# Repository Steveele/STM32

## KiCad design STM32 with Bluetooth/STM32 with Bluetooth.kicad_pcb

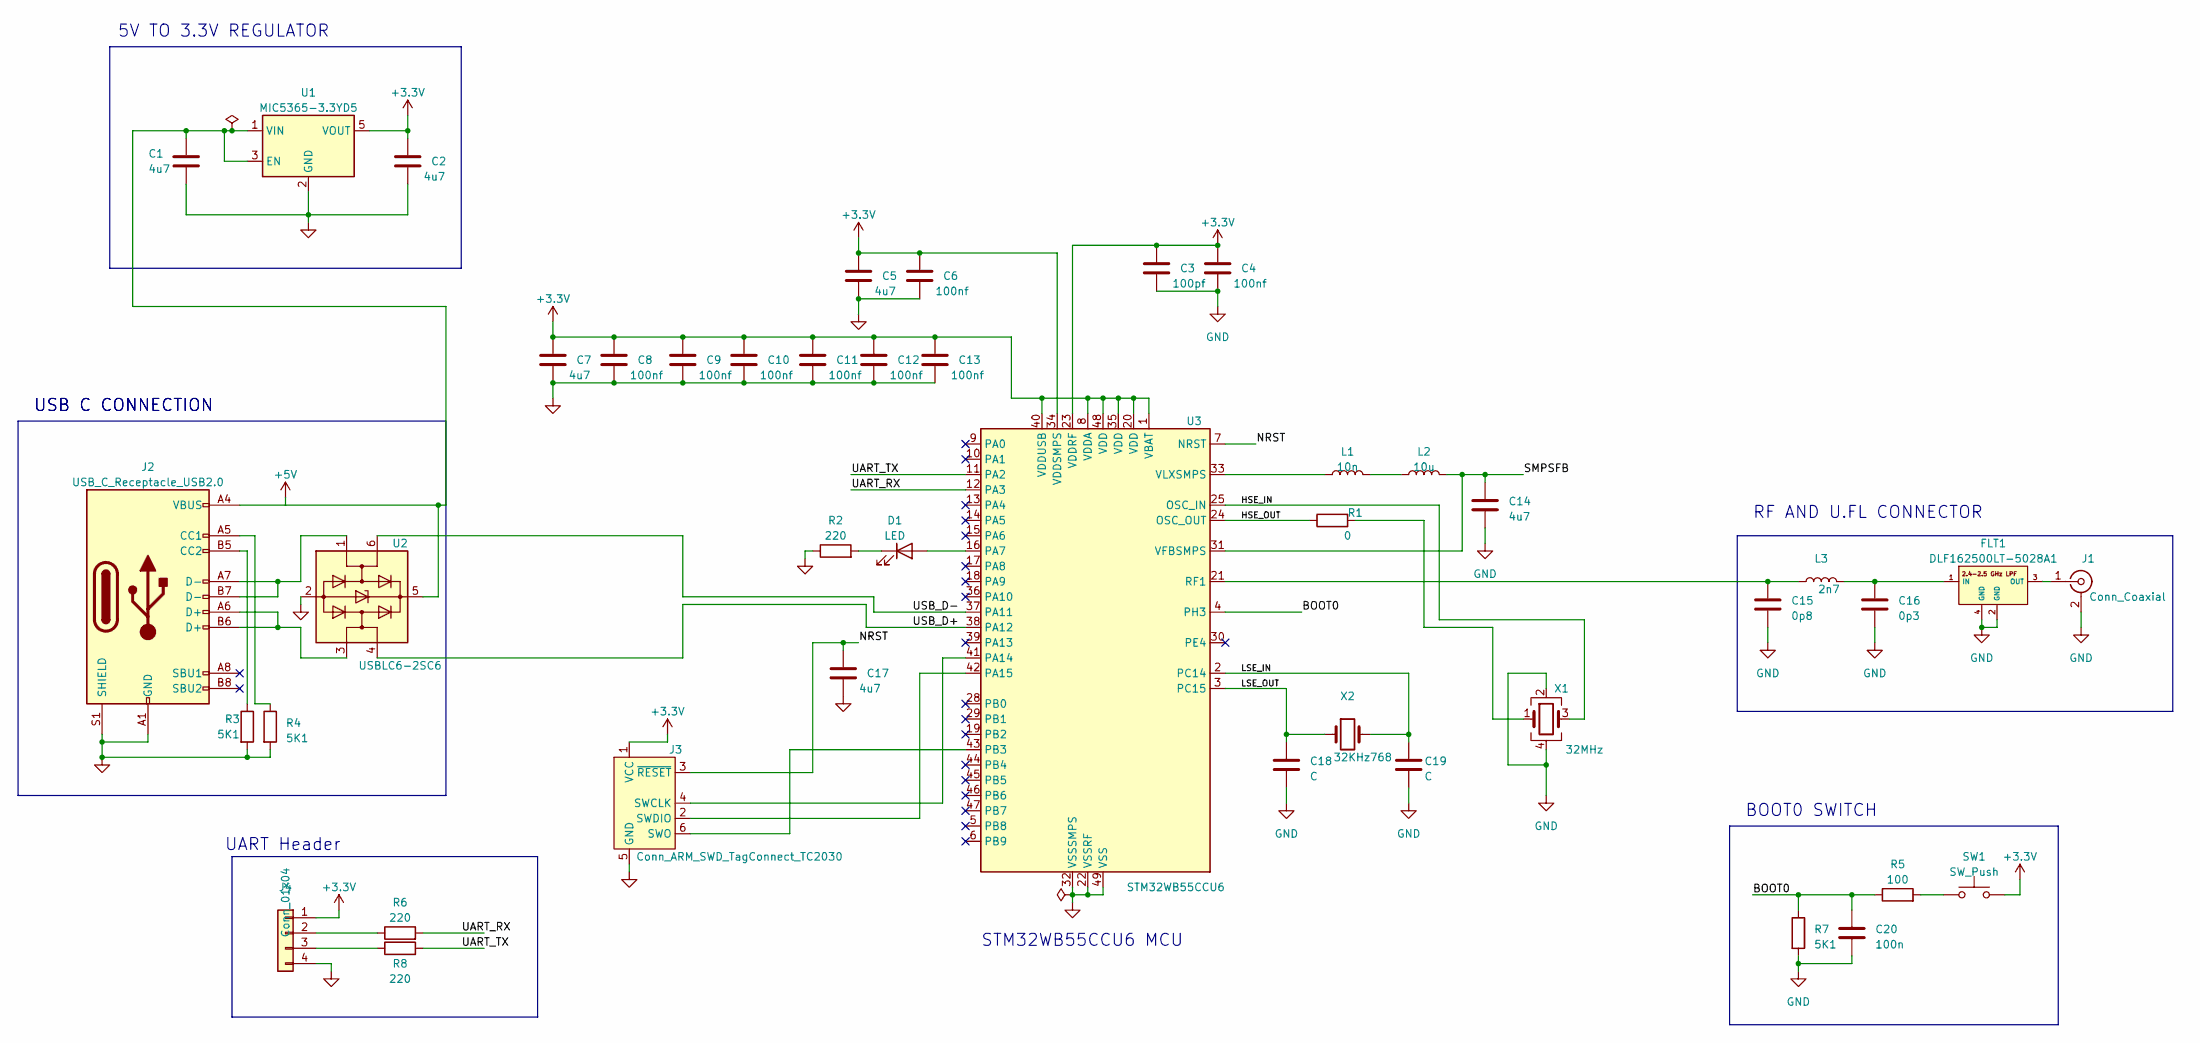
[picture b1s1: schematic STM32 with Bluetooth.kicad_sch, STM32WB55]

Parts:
C1, C2, C5, C7, C14, C17: 4u7; C_0603_1608Metric
C3: 100pf; C_0402_1005Metric
C4, C6, C8, C9, C10, C11, C12, C13: 100nf; C_0402_1005Metric
C15: 0p8; C_0402_1005Metric
C16: 0p3; C_0402_1005Metric
C18, C19: C; C_0402_1005Metric
C20: 100n; C_0402_1005Metric
D1: LED; LED_0402_1005Metric
FLT1: DLF162500LT-5028A1
J1: Conn_Coaxial; U.FL_Hirose_U.FL-R-SMT-1_Vertical
J2: USB_C_Receptacle_USB2.0; USB_C_Receptacle_GCT_USB4105-xx-A_16P_TopMnt_Horizontal
J3: Conn_ARM_SWD_TagConnect_TC2030; Tag-Connect_TC2030-IDC-FP_2x03_P1.27mm_Vertical
J4: Conn_01x04; Molex_PicoBlade_53048-0410_1x04_P1.25mm_Horizontal
L1: 10n; L_0402_1005Metric
L2: 10u; L_0402_1005Metric
L3: 2n7; L_0402_1005Metric
R1: 0; R_0402_1005Metric
R2, R6, R8: 220; R_0402_1005Metric
R3, R4, R7: 5K1; R_0402_1005Metric
R5: 100; R_0402_1005Metric
SW1: SW_Push; SW_SPST_CK_RS282G05A3
U1: MIC5365-3.3YD5; SOT-23-5
U2: USBLC6-2SC6; SOT-23-6
U3: STM32WB55CCU6; QFN-48-1EP_7x7mm_P0.5mm_EP5.6x5.6mm
X1: 32MHz; Crystal_SMD_2016-4Pin_2.0x1.6mm
X2: 32KHz768; Crystal_SMD_2012-2Pin_2.0x1.2mm

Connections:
+3.3V: C2.1, C3.1, C4.1, C5.1, C6.1, C7.1, C8.1, C9.1, C10.1, C11.1, C12.1, C13.1, J3.1 (VCC), J4.1, SW1.2, U1.5 (VOUT), U3.1 (VBAT), U3.8 (VDDA), U3.20 (VDD), U3.23 (VDDRF), U3.34 (VDDSMPS), U3.35 (VDD), U3.40 (VDDUSB), U3.48 (VDD)
/BOOT0: C20.1, R5.1, R7.1, U3.4 (PH3)
/HSE_IN: U3.25 (OSC_IN), X1.3
/HSE_OUT: R1.1, R1.2, U3.24 (OSC_OUT), X1.1
/LSE_IN: C19.1, U3.2 (PC14), X2.2
/LSE_OUT: C18.1, U3.3 (PC15), X2.1
/NRST: C17.1, J3.3 (~RESET), U3.7 (NRST)
/SMPSFB: C14.1, L2.2, U3.31 (VFBSMPS)
/UART_RX: R6.2, U3.12 (PA3)
/UART_TX: R8.2, U3.11 (PA2)
/USB_D+: U2.4 (I/O2), U3.38 (PA12)
/USB_D-: U2.6 (I/O1), U3.37 (PA11)
GND: C1.2, C2.2, C3.2, C4.2, C5.2, C6.2, C7.2, C8.2, C9.2, C10.2, C11.2, C12.2, C13.2, C14.2, C15.2, C16.2, C17.2, C18.2, C19.2, C20.2, FLT1.2 (GND), FLT1.4 (GND), J1.2 (Ext), J2.A1 (GND), J2.A12 (GND), J2.B1 (GND), J2.B12 (GND), J2.S1 (SHIELD), J3.5 (GND), J4.4, R2.1, R3.2, R4.2, R7.2, U1.2 (GND), U2.2 (GND), U3.22 (VSSRF), U3.32 (VSSSMPS), U3.49 (VSS), X1.2, X1.4
unnamed: D1.2 (A), U3.16 (PA7)
unnamed: D1.1 (K), R2.2
unnamed: C16.1, FLT1.1 (IN), L3.2
unnamed: FLT1.3 (OUT), J1.1 (In)
unnamed: J2.A5 (CC1), R4.1
unnamed: J2.B5 (CC2), R3.1
unnamed: J2.A6 (D+), J2.B6 (D+), U2.3 (I/O2)
unnamed: J2.A7 (D-), J2.B7 (D-), U2.1 (I/O1)
unnamed: J3.4 (SWCLK), U3.41 (PA14)
unnamed: J3.6 (SWO), U3.43 (PB3)
unnamed: J4.2, R6.1
unnamed: J4.3, R8.1
unnamed: L1.2, L2.1
unnamed: R5.2, SW1.1
unnamed: C1.1, J2.A4 (VBUS), J2.A9 (VBUS), J2.B4 (VBUS), J2.B9 (VBUS), U1.1 (VIN), U1.3 (EN), U2.5 (VBUS)
unnamed: C15.1, L3.1, U3.21 (RF1)
unnamed: L1.1, U3.33 (VLXSMPS)

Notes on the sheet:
BOOT0 SWITCH
USB C CONNECTION
UART Header
RF AND U.FL CONNECTOR
5V TO 3.3V REGULATOR
STM32WB55CCU6 MCU

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
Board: 4 copper layers, 42 parts (0 on the bottom side), 31 nets, no tracks yet.

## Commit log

2023-12-19 initial
2023-12-20 Microcontroller power
2023-12-21 filter library
2023-12-22 FLT library
2023-12-25 Usb connector
2023-12-25 git ignore
2023-12-25 final schematics
2023-12-26 Electrical rule checked
2023-12-26 componnent assignment
